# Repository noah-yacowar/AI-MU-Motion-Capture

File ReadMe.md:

# The "AI-MU" Motion-Capture Project

ESP8266 + BNO08x (080/085) based motion capture system that streams IMU data over Wi-Fi into Unity.  
The ecosystem includes a **mobile app** for QR code–based pairing of IMU suits and servers, making setup fast and reliable. This was chosen especially for commercial use cases where multiple users will be using the system daily. Here, a simple fixed connection from the sensor directly to the server is not flexible enough for all workflows.
The Unity application performs real-time skeleton reconstruction, visualization, and recording, with the ability to export captured motion to **BVH** for animation workflows.

---

## 📸 Overview

*Custom ESP8266 D1 Mini + BNO08x tracker module*

*Unity interface showing live skeleton and recording controls*

*Mobile app used to scan QR code of IMU suit and connect to server*

---

## ✨ Features

- **Low-cost IMU Trackers**: ESP8266 D1 Mini boards with BNO080/BNO085 IMUs.
- **Mobile App Integration**: Scan a QR code on the IMU suit to automatically configure and connect to the server.  
- **Wi-Fi Data Streaming**: Fast UDP packets (~100 Hz) from multiple trackers.
- **Real-time Visualization**: Unity app reconstructs skeletons live.
- **Calibration Tools**: Mounting error correction + baseline yaw alignment.
- **Multi-Participant Support**: Capture multiple people simultaneously.
- **Recording & Export**: Save sessions and export to **BVH** (for Blender, Unity, Maya, etc.).

---

## 🖥️ Software

- **Firmware**: C++/Arduino code running on each D1 Mini, sending IMU quaternions via UDP.  
- **Mobile App**:  
  - Scans QR code on the IMU suit to register tracker IDs.  
  - Connects suit to the Unity server automatically.  
- **Unity App**:  
  - Receives tracker data  
  - Maps IMUs to skeleton joints  
  - Provides calibration tools  
  - Records sessions and exports animations  

---

## 📦 Hardware

Each tracker is built from:

- **ESP8266 D1 Mini (Wemos)**  
- **BNO080 / BNO085 IMU sensor** (I²C connection)  
- **Battery + charging module**  
- 3D printed case (friction-fit lid for quick access)  

📷 Images:  

*Friction-fit printed case for tracker module*

*PCB layout in Kicad*

---

## 🚀 Getting Started

### 1. Clone the Repository
```bash
git clone https://github.com/noah-yacowar/AI-MU-Motion-Capture.git
cd AI-MU-Motion-Capture

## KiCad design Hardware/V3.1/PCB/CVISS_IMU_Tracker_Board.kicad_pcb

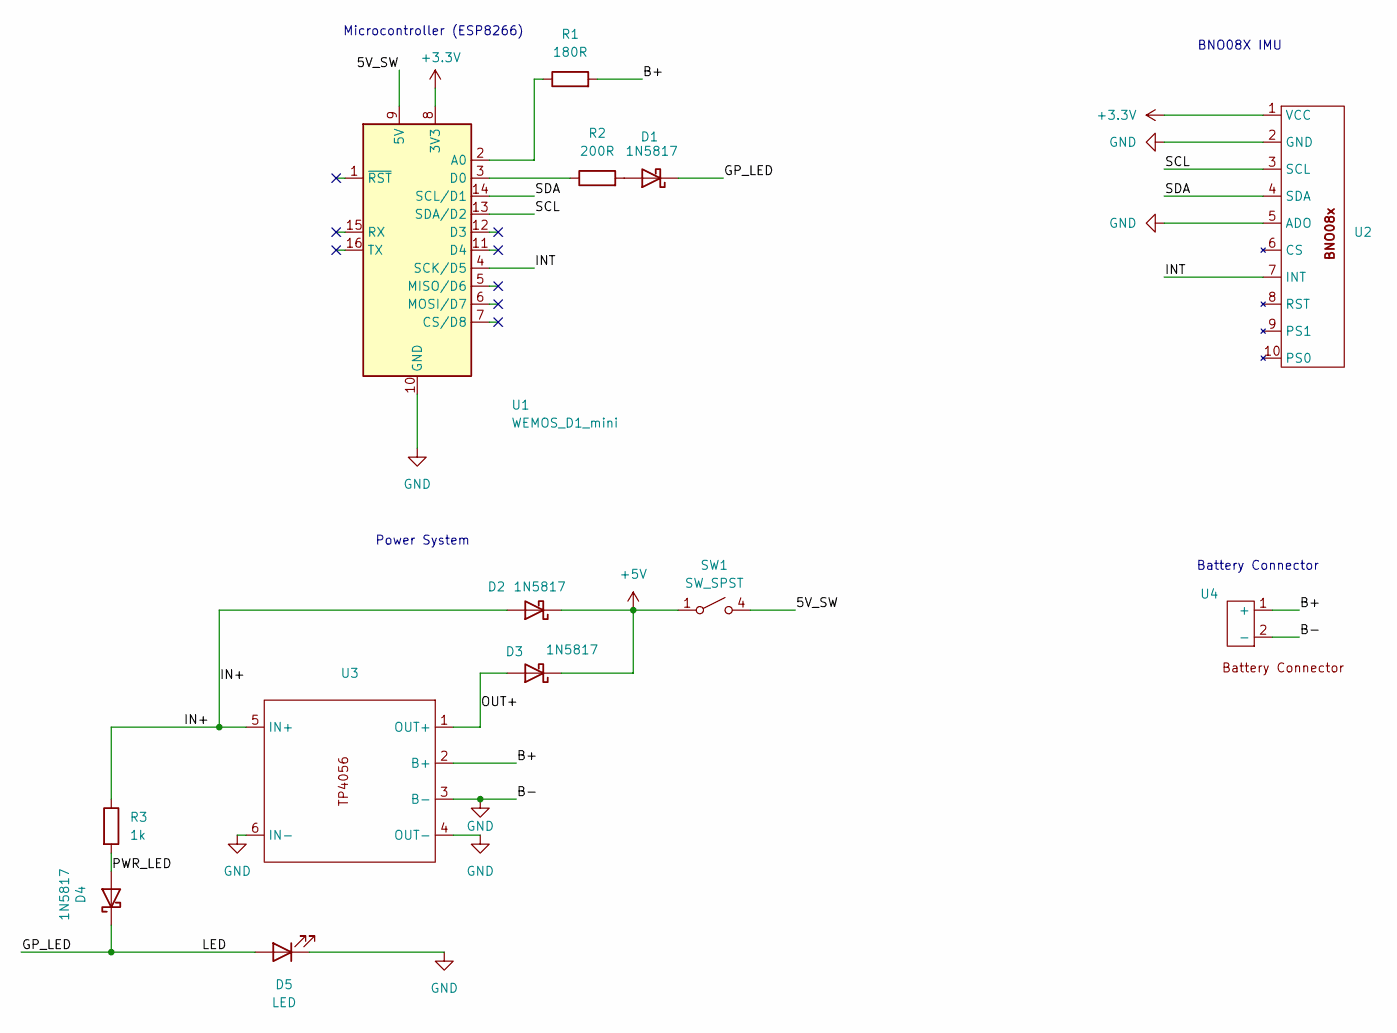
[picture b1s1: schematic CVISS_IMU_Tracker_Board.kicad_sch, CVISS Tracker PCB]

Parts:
D1, D2, D3, D4: 1N5817; D_DO-41_SOD81_P10.16mm_Horizontal
D5: LED; LED_D5.0mm_Clear
R1: 180R; R_Axial_DIN0207_L6.3mm_D2.5mm_P7.62mm_Horizontal
R2: 200R; R_Axial_DIN0207_L6.3mm_D2.5mm_P7.62mm_Horizontal
R3: 1k; R_Axial_DIN0207_L6.3mm_D2.5mm_P7.62mm_Horizontal
SW1: SW_SPST; SK12DO7_Switch
U1: WEMOS_D1_mini; WEMOS_D1_mini_light
U2: BNO08x_Board
U3: TP4056_Board
U4: Battery_Connector

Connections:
+3.3V: U1.8 (3V3), U2.1 (VCC)
+5V: D2.1 (K), D3.1 (K), SW1.1 (A)
/5V_SW: SW1.4 (B), U1.9 (5V)
/B+: R1.2, U3.2 (B+), U4.1 (+)
/GP_LED: D1.1 (K), D4.1 (K), D5.2 (A)
/IN+: D2.2 (A), R3.1, U3.5 (IN+)
/INT: U1.4 (SCK/D5), U2.7 (INT)
/OUT+: D3.2 (A), U3.1 (OUT+)
/PWR_LED: D4.2 (A), R3.2
/SCL: U1.13 (SDA/D2), U2.3 (SCL)
/SDA: U1.14 (SCL/D1), U2.4 (SDA)
GND: D5.1 (K), U1.10 (GND), U2.2 (GND), U2.5 (ADO), U3.3 (B-), U3.4 (OUT-), U3.6 (IN-), U4.2 (-)
unnamed: D1.2 (A), R2.2
unnamed: R1.1, U1.2 (A0)
unnamed: R2.1, U1.3 (D0)

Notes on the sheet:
BNO08X IMU
Power System
Microcontroller (ESP8266)
Battery Connector

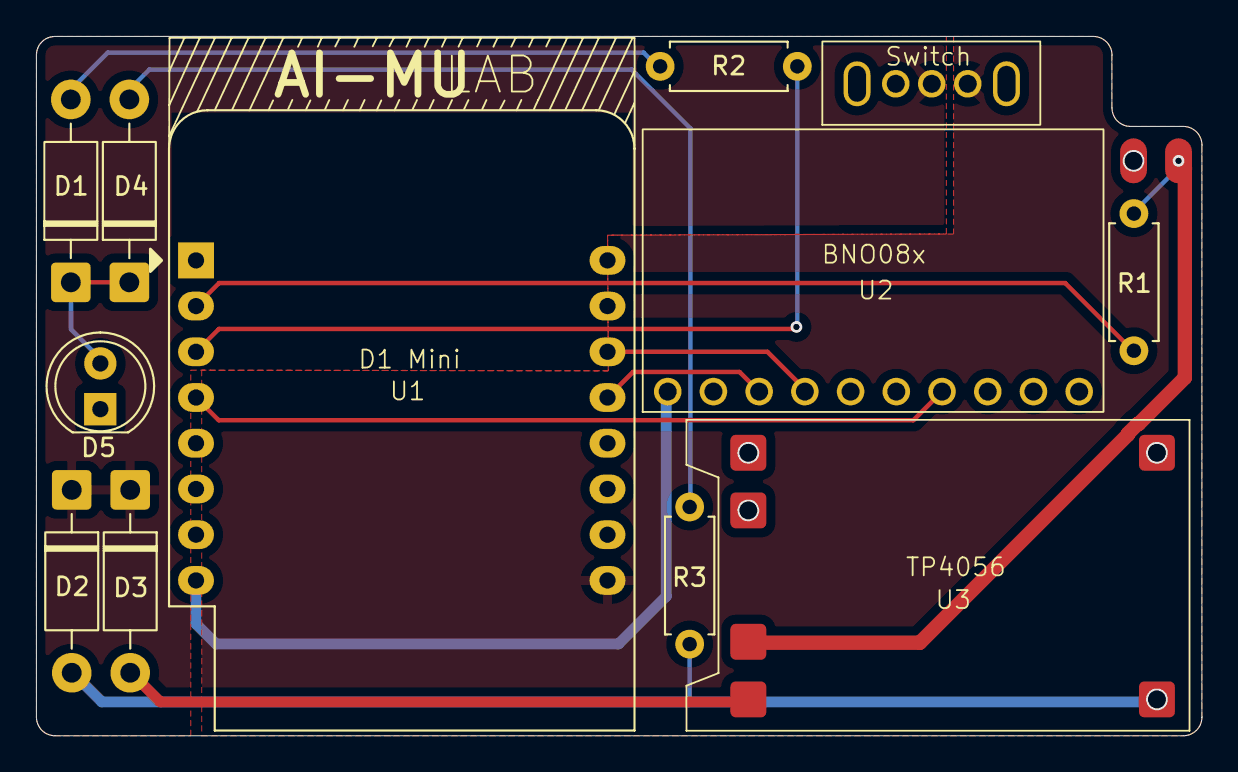
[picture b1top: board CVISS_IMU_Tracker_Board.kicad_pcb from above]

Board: 2 copper layers, 64.7 x 38.9 mm, 13 parts (0 on the bottom side), 15 nets.

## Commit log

2025-09-02 Add readme
2025-09-02 Remove HR and camera feed
2025-09-02 Remove video script in scene
2025-09-02 Update mobile app intro icon
2025-09-02 Remove unecessary pages
2025-09-06 Server fix side panel UI
2025-09-08 Removed bloat
2025-09-11 Electronics folder
2025-09-11 Add images, update readme
2025-09-11 Update tracker.jpg rotation
2025-09-11 Update reame
2025-09-11 Update reame images
2025-09-11 Remove g code
2025-09-11 Add PCB to readme
